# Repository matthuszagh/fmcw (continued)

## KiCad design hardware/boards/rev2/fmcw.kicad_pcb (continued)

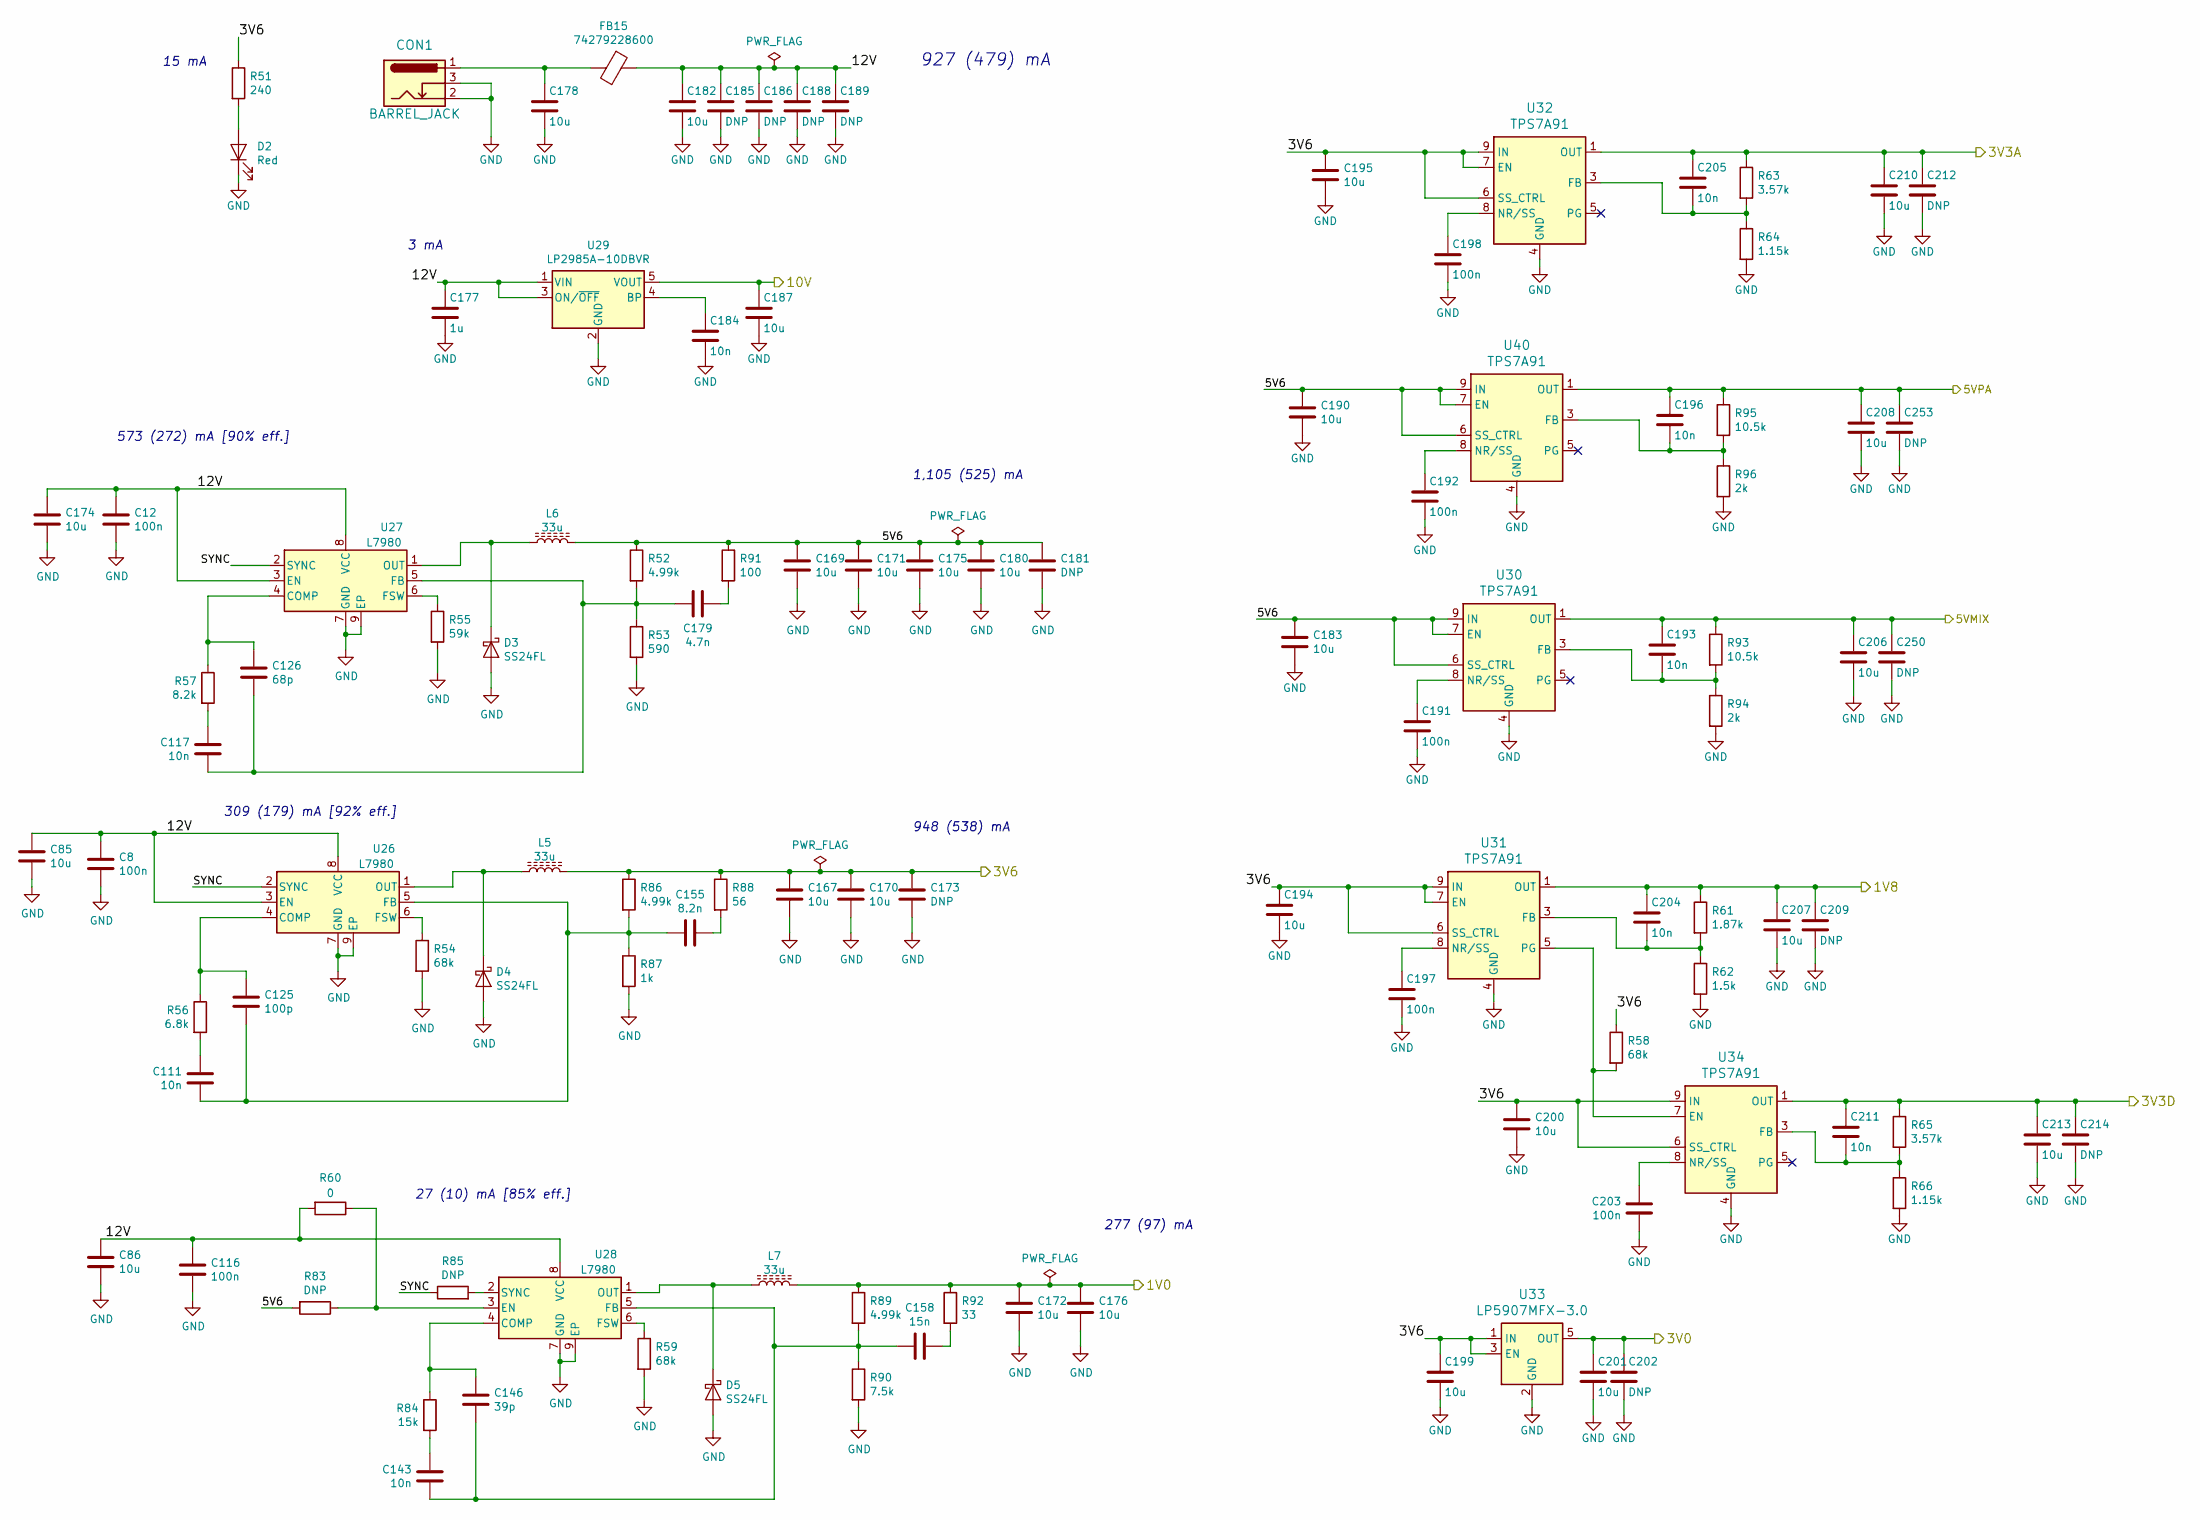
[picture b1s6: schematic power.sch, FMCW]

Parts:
C8, C12, C116, C191, C192, C197, C198, C203: 100n; C_0402_1005Metric
C85, C86, C167, C169, C170, C171, C172, C174, C175, C176, C178, C180, C182, C183, C187, C190, C194, C195, C199, C200, C201, C206, C207, C208, C210, C213: 10u; C_0805_2012Metric
C111, C117, C143, C184, C193, C196, C204, C205, C211: 10n; C_0402_1005Metric
C125: 100p; C_0402_1005Metric
C126: 68p; C_0402_1005Metric
C146: 39p; C_0402_1005Metric
C155: 8.2n; C_0402_1005Metric
C158: 15n; C_0402_1005Metric
C173, C181, C185, C186, C188, C189, C202, C209, C212, C214, C250, C253: DNP; C_0805_2012Metric
C177: 1u; C_0603_1608Metric
C179: 4.7n; C_0402_1005Metric
CON1: BARREL_JACK; BarrelJack_Wuerth_6941xx301002
D2: Red; LED_0603_1608Metric
D3, D4, D5: SS24FL; D_SOD-123F
FB15: 74279228600; L_0603_1608Metric
L5, L6: 33u; L_Wuerth_HCI-1365
L7: 33u; SRR6040A
R51: 240; R_0402_1005Metric
R52, R86, R89: 4.99k; R_0402_1005Metric
R53: 590; R_0402_1005Metric
R54, R58, R59: 68k; R_0402_1005Metric
R55: 59k; R_0402_1005Metric
R56: 6.8k; R_0402_1005Metric
R57: 8.2k; R_0402_1005Metric
R60: 0; R_0402_1005Metric
R61: 1.87k; R_0402_1005Metric
R62: 1.5k; R_0402_1005Metric
R63, R65: 3.57k; R_0402_1005Metric
R64, R66: 1.15k; R_0402_1005Metric
R83, R85: DNP; R_0402_1005Metric
R84: 15k; R_0402_1005Metric
R87: 1k; R_0402_1005Metric
R88: 56; R_0402_1005Metric
R90: 7.5k; R_0402_1005Metric
R91: 100; R_0402_1005Metric
R92: 33; R_0402_1005Metric
R93, R95: 10.5k; R_0402_1005Metric
R94, R96: 2k; R_0402_1005Metric
U26, U27, U28: L7980; HSOP-8-1EP_3.9x4.9mm_P1.27mm_EP2.3x2.3mm_ThermalVias
U29: LP2985A-10DBVR; SOT-23-5
U30, U31, U32, U34, U40: TPS7A91; Texas_S-PDSO-N10_EP1.2x2mm
U33: LP5907MFX-3.0; SOT-23-5

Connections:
/1V0: C172.1, C176.1, L7.2, R89.1, R92.1; also elsewhere on the board
/1V8: C204.1, C207.1, C209.1, R61.1, U31.1 (OUT), U31.2 (OUT); also elsewhere on the board
/3V0: C201.1, C202.1, U33.5 (OUT); also elsewhere on the board
/3V3A: C205.1, C210.1, C212.1, R63.1, U32.1 (OUT), U32.2 (OUT); also elsewhere on the board
/3V6: C167.1, C170.1, C173.1, C194.1, C195.1, C199.1, C200.1, L5.2, R51.1, R58.1, R86.1, R88.1, U31.6 (SS_CTRL), U31.7 (EN), U31.9 (IN), U31.10 (IN), U32.6 (SS_CTRL), U32.7 (EN), U32.9 (IN), U32.10 (IN), U33.1 (IN), U33.3 (EN), U34.6 (SS_CTRL), U34.9 (IN), U34.10 (IN); also elsewhere on the board
/5VMIX: C193.1, C206.1, C250.1, R93.1, U30.1 (OUT), U30.2 (OUT); also elsewhere on the board
/5VPA: C196.1, C208.1, C253.1, R95.1, U40.1 (OUT), U40.2 (OUT); also elsewhere on the board
/10V: C187.1, U29.5 (VOUT); also elsewhere on the board
/power/5V6: C169.1, C171.1, C175.1, C180.1, C181.1, C183.1, C190.1, L6.2, R52.1, R83.2, R91.1, U30.6 (SS_CTRL), U30.7 (EN), U30.9 (IN), U30.10 (IN), U40.6 (SS_CTRL), U40.7 (EN), U40.9 (IN), U40.10 (IN)
/power/12V: C8.1, C12.1, C85.1, C86.1, C116.1, C174.1, C177.1, C182.1, C185.1, C186.1, C188.1, C189.1, FB15.1, R60.2, U26.3 (EN), U26.8 (VCC), U27.3 (EN), U27.8 (VCC), U28.8 (VCC), U29.1 (VIN), U29.3 (ON/~OFF~)
/power/SYNC: R85.1, U26.2 (SYNC), U27.2 (SYNC)
GND: C8.2, C12.2, C85.2, C86.2, C116.2, C167.2, C169.2, C170.2, C171.2, C172.2, C173.2, C174.2, C175.2, C176.2, C177.2, C178.2, C180.2, C181.2, C182.2, C183.2, C184.2, C185.2, C186.2, C187.2, C188.2, C189.2, C190.2, C191.2, C192.2, C194.2, C195.2, C197.2, C198.2, C199.2, C200.2, C201.2, C202.2, C203.2, C206.2, C207.2, C208.2, C209.2, C210.2, C212.2, C213.2, C214.2, C250.2, C253.2, CON1.2, CON1.3, D2.1 (K), D3.2 (A), D4.2 (A), D5.2 (A), R53.2, R54.2, R55.2, R59.2, R62.2, R64.2, R66.2, R87.2, R90.2, R94.2, R96.2, U26.7 (GND), U26.9 (EP), U27.7 (GND), U27.9 (EP), U28.7 (GND), U28.9 (EP), U29.2 (GND), U30.4 (GND), U30.11 (GND), U31.4 (GND), U31.11 (GND), U32.4 (GND), U32.11 (GND), U33.2 (GND), U34.4 (GND), U34.11 (GND), U40.4 (GND), U40.11 (GND); also elsewhere on the board
unnamed: C111.1, R56.2
unnamed: C111.2, C125.2, C155.2, R86.2, R87.1, U26.5 (FB)
unnamed: C117.1, R57.2
unnamed: C117.2, C126.2, C179.2, R52.2, R53.1, U27.5 (FB)
unnamed: C125.1, R56.1, U26.4 (COMP)
unnamed: C126.1, R57.1, U27.4 (COMP)
unnamed: C143.1, R84.2
unnamed: C143.2, C146.2, C158.2, R89.2, R90.1, U28.5 (FB)
unnamed: C146.1, R84.1, U28.4 (COMP)
unnamed: C155.1, R88.2
unnamed: C158.1, R92.2
unnamed: C178.1, CON1.1, FB15.2
unnamed: C179.1, R91.2
unnamed: C184.1, U29.4 (BP)
unnamed: C191.1, U30.8 (NR/SS)
unnamed: C192.1, U40.8 (NR/SS)
unnamed: C193.2, R93.2, R94.1, U30.3 (FB)
unnamed: C196.2, R95.2, R96.1, U40.3 (FB)
unnamed: C197.1, U31.8 (NR/SS)
unnamed: C198.1, U32.8 (NR/SS)
unnamed: C203.1, U34.8 (NR/SS)
unnamed: C204.2, R61.2, R62.1, U31.3 (FB)
unnamed: C205.2, R63.2, R64.1, U32.3 (FB)
unnamed: C211.2, R65.2, R66.1, U34.3 (FB)
unnamed: D2.2 (A), R51.2
unnamed: D3.1 (K), L6.1, U27.1 (OUT)
unnamed: D4.1 (K), L5.1, U26.1 (OUT)
unnamed: D5.1 (K), L7.1, U28.1 (OUT)
unnamed: R54.1, U26.6 (FSW)
unnamed: R55.1, U27.6 (FSW)
unnamed: R58.2, U31.5 (PG), U34.7 (EN)
unnamed: R59.1, U28.6 (FSW)
unnamed: R60.1, R83.1, U28.3 (EN)
unnamed: R85.2, U28.2 (SYNC)

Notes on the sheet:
573 (272) mA [90% eff.]
15 mA
309 (179) mA [92% eff.]
3 mA
27 (10) mA [85% eff.]
1,105 (525) mA
948 (538) mA
927 (479) mA
277 (97) mA

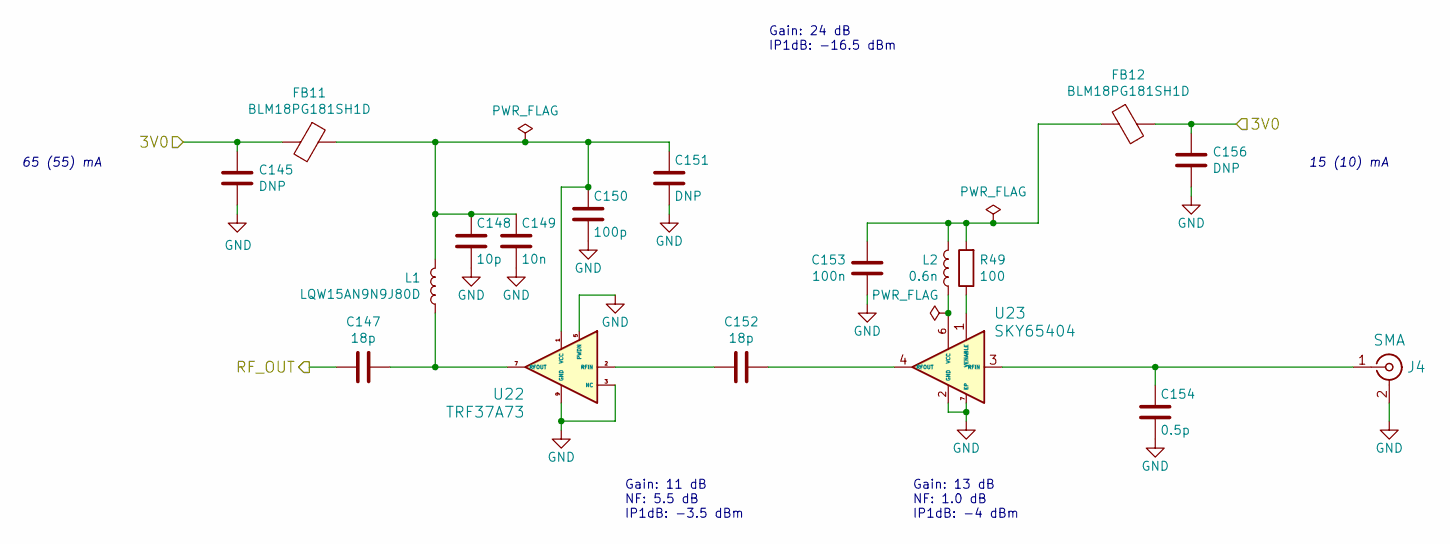
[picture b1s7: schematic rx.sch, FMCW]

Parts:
C145, C156: DNP; C_0805_2012Metric
C147, C152: 18p; RF_C_0201_0603Metric
C148: 10p; C_0402_1005Metric
C149: 10n; C_0402_1005Metric
C150: 100p; C_0402_1005Metric
C153: 100n; C_0402_1005Metric
C154: 0.5p; RF_C_0201_0603Metric
C163: DNP; C_0603_1608Metric
FB13, FB14: BLM18PG181SH1D; L_0603_1608Metric
J4: SMA; SMA_901-10512
L1: LQW15AN9N9J80D; RF_Bypass_C_0402_1005Metric
L2: 0.6n; L_0402_1005Metric
R49: 100; R_0402_1005Metric
U22: TRF37A73; WSON-8-1EP_2x2mm_P0.5mm_EP0.9x1.6mm_ThermalVias
U23: SKY65404; Skyworks_SKY65404-31

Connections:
/3V0: C145.1, C156.1, FB13.2, FB14.2; also elsewhere on the board
/RF1: C147.2; also elsewhere on the board
GND: C145.2, C148.2, C149.2, C150.2, C153.2, C154.2, C156.2, C163.2, J4.2 (Ext), U22.3 (NC), U22.4 (NC), U22.5 (PWDN), U22.6 (NC), U22.8 (NC), U22.9 (GND), U23.2 (GND), U23.5 (GND), U23.7 (EP); also elsewhere on the board
unnamed: C147.1, L1.1, U22.7 (RFOUT)
unnamed: C152.1, U23.4 (RFOUT)
unnamed: C152.2, U22.2 (RFIN)
unnamed: C154.1, J4.1 (In), U23.3 (RFIN)
unnamed: L2.1, U23.6 (VCC)
unnamed: R49.1, U23.1 (VENABLE)

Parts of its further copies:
C151: DNP; C_0603_1608Metric
C157, C168: DNP; C_0805_2012Metric
C159, C164: 18p; RF_C_0201_0603Metric
C160: 10p; C_0402_1005Metric
C161: 10n; C_0402_1005Metric
C162: 100p; C_0402_1005Metric
C165: 100n; C_0402_1005Metric
C166: 0.5p; RF_C_0201_0603Metric
FB11, FB12: BLM18PG181SH1D; L_0603_1608Metric
J5: SMA; SMA_901-10512
L3: LQW15AN9N9J80D; RF_Bypass_C_0402_1005Metric
L4: 0.6n; L_0402_1005Metric
R50: 100; R_0402_1005Metric
U24: TRF37A73; WSON-8-1EP_2x2mm_P0.5mm_EP0.9x1.6mm_ThermalVias
U25: SKY65404; Skyworks_SKY65404-31

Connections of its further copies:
/3V0: C157.1, C168.1, FB11.2, FB12.2; also elsewhere on the board
/RF2: C159.2; also elsewhere on the board
GND: C151.2, C157.2, C160.2, C161.2, C162.2, C165.2, C166.2, C168.2, J5.2 (Ext), U24.3 (NC), U24.4 (NC), U24.5 (PWDN), U24.6 (NC), U24.8 (NC), U24.9 (GND), U25.2 (GND), U25.5 (GND), U25.7 (EP); also elsewhere on the board
unnamed: C159.1, L3.1, U24.7 (RFOUT)
unnamed: C164.1, U25.4 (RFOUT)
unnamed: C164.2, U24.2 (RFIN)
unnamed: C166.1, J5.1 (In), U25.3 (RFIN)
unnamed: L4.1, U25.6 (VCC)
unnamed: R50.1, U25.1 (VENABLE)

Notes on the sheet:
65 (55) mA
Gain: 11 dB NF: 5.5 dB IP1dB: -3.5 dBm
Gain: 24 dB IP1dB: -16.5 dBm
Gain: 13 dB NF: 1.0 dB IP1dB: -4 dBm
15 (10) mA

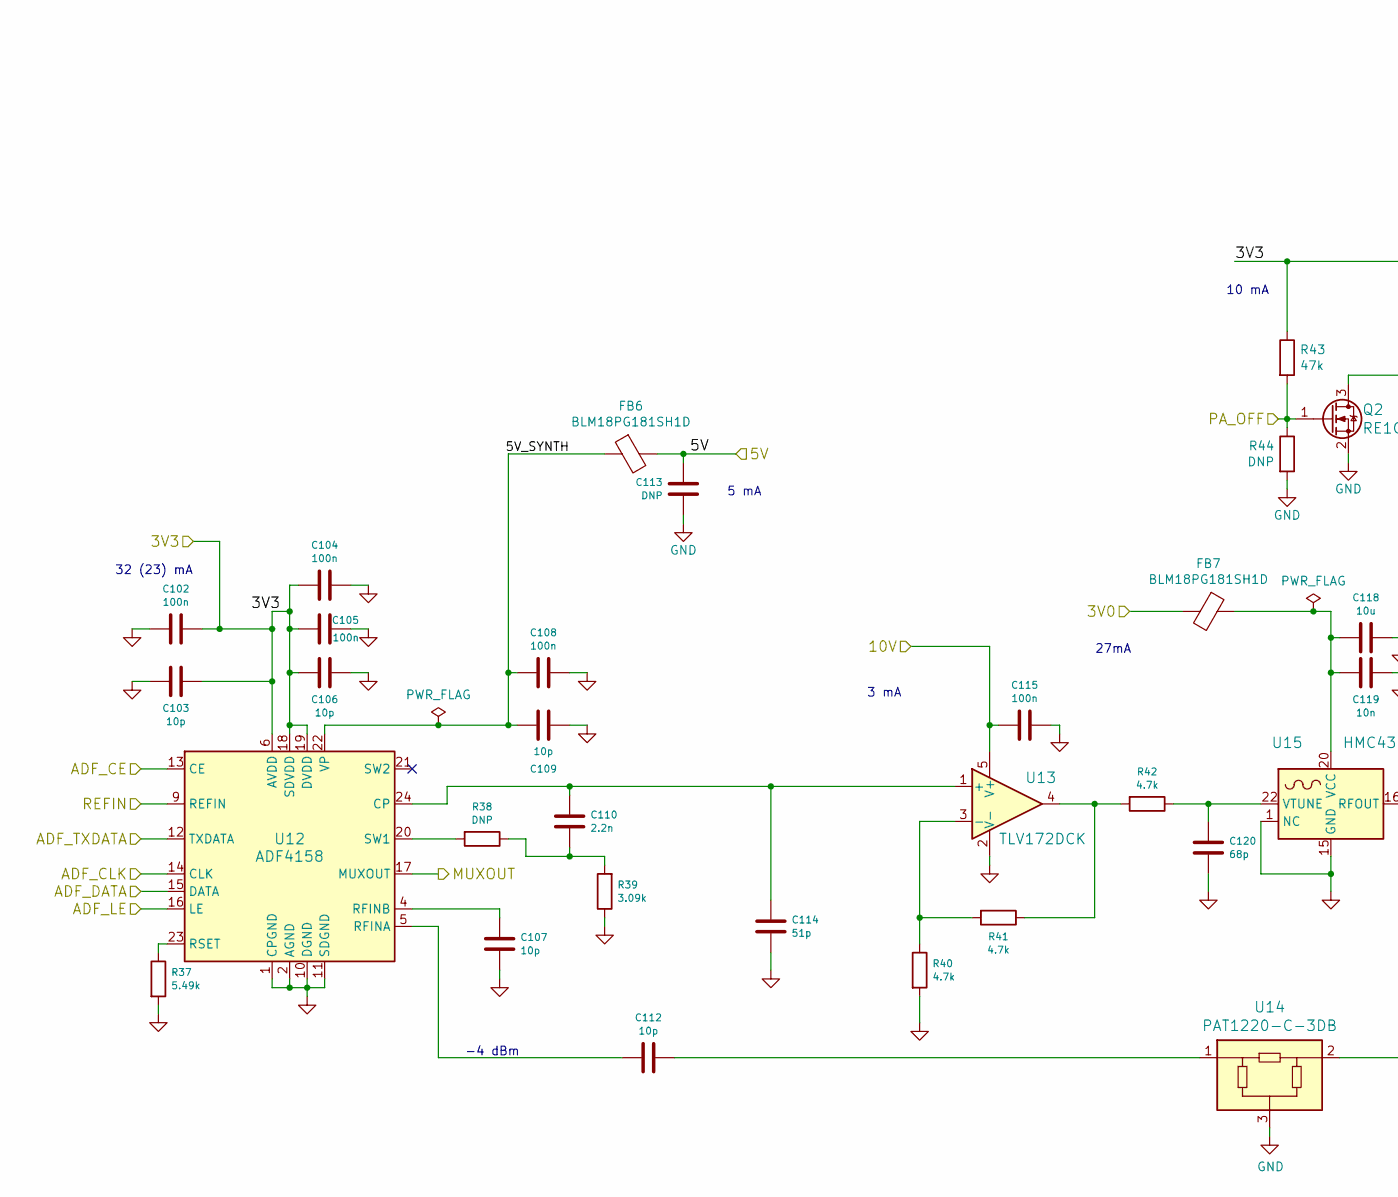
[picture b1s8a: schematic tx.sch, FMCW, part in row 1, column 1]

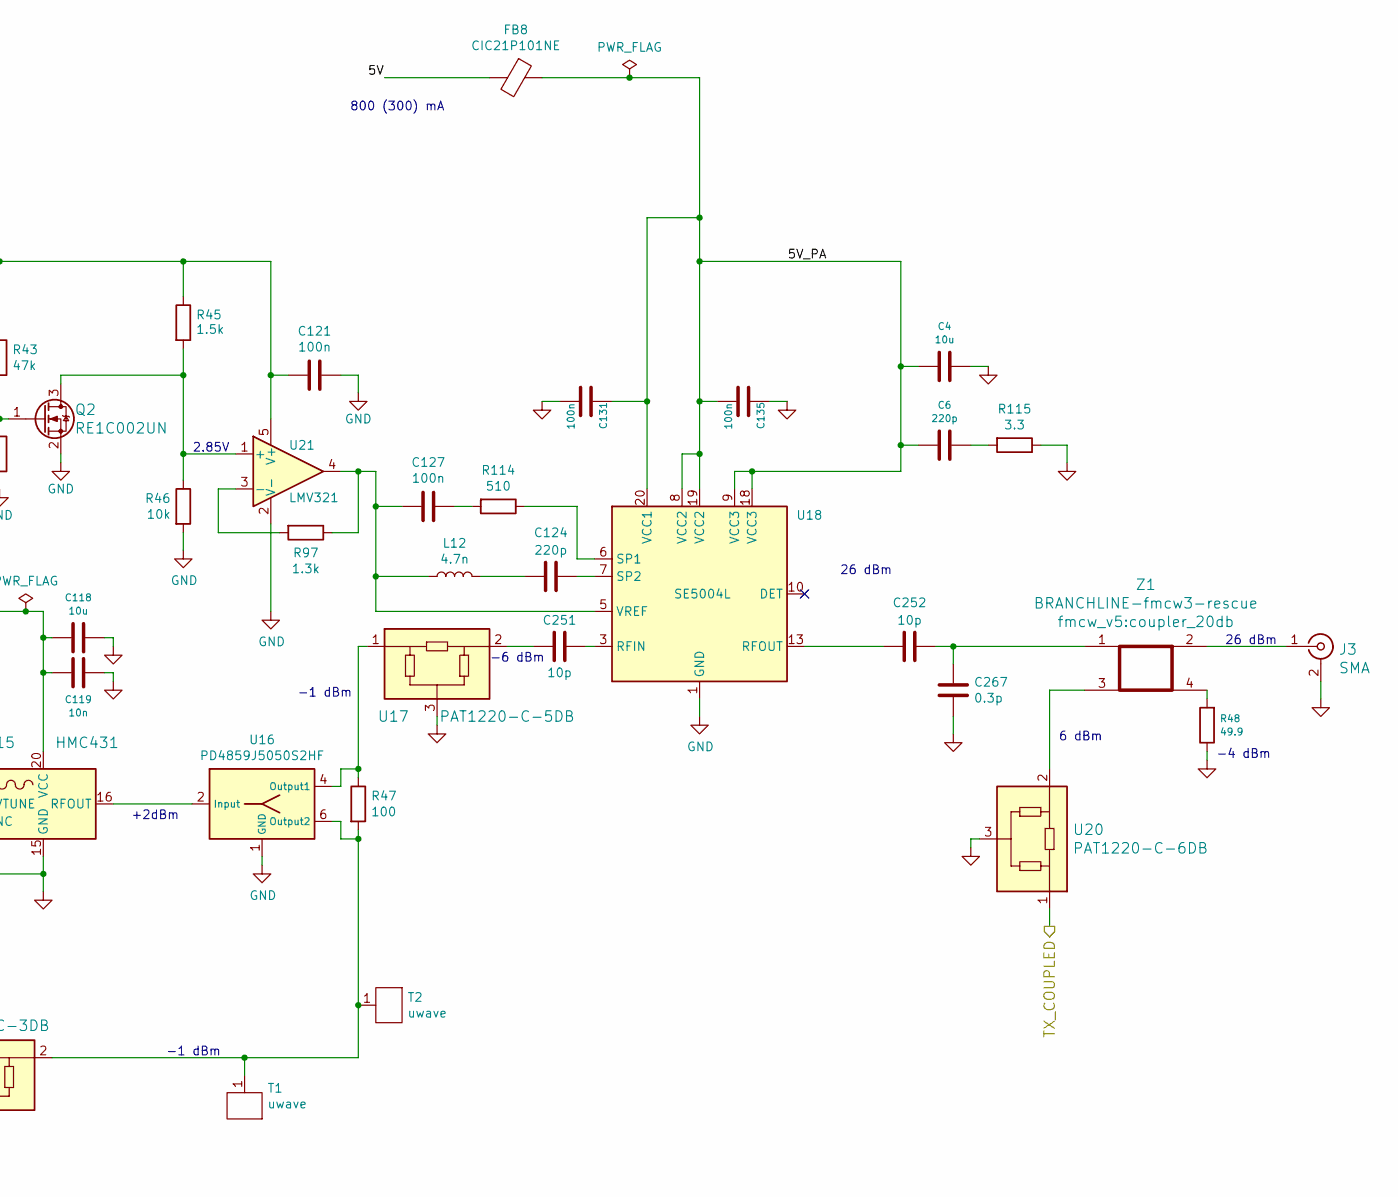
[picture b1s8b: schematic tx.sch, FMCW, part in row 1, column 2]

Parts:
C4, C118: 10u; C_0805_2012Metric
C6, C124: 220p; C_0402_1005Metric
C102, C104, C105, C108, C115, C121, C127, C131, C135: 100n; C_0402_1005Metric
C103, C106, C107, C109: 10p; C_0402_1005Metric
C110: 2.2n; C_0402_1005Metric
C112, C251, C252: 10p; RF_C_0201_0603Metric
C113: DNP; C_0805_2012Metric
C114: 51p; C_0402_1005Metric
C119: 10n; C_0402_1005Metric
C120: 68p; C_0402_1005Metric
C267: 0.3p; RF_C_0201_0603Metric
FB6, FB7: BLM18PG181SH1D; L_0603_1608Metric
FB8: CIC21P101NE; L_0805_2012Metric
J3: SMA; SMA_901-10512
L12: 4.7n; L_0402_1005Metric
Q2: RE1C002UN; SOT-416
R37: 5.49k; R_0402_1005Metric
R38, R44: DNP; R_0402_1005Metric
R39: 3.09k; R_0402_1005Metric
R40, R41, R42: 4.7k; R_0402_1005Metric
R43: 47k; R_0402_1005Metric
R45: 1.5k; R_0402_1005Metric
R46: 10k; R_0402_1005Metric
R47: 100; R_0603b
R48: 49.9; R_0402_1005Metric
R97: 1.3k; R_0402_1005Metric
R114: 510; R_0402_1005Metric
R115: 3.3; R_0402_1005Metric
T1, T2: uwave; uwm_0.38_0.17_90
U12: ADF4158; LFCSP-24-1EP_4x4mm_P0.5mm_EP2.5x2.5mm_ThermalVias
U13: TLV172DCK; SOT-353_SC-70-5
U14: PAT1220-C-3DB; RF_Attenuator_Susumu_PAT1220
U15: HMC431; QFN-24-1EP_4x4mm_P0.5mm_EP2.8x2.8mm_ThermalVias
U16: PD4859J5050S2HF; Anaren_0805_2012Metric-6
U17: PAT1220-C-5DB; RF_Attenuator_Susumu_PAT1220
U18: SE5004L; Skyworks_SE5004L
U20: PAT1220-C-6DB; RF_Attenuator_Susumu_PAT1220
U21: LMV321; SOT-23-5
Z1: BRANCHLINE-fmcw3-rescue; coupler_20db

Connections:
/3V0: FB7.2; also elsewhere on the board
/3V3A: C102.1, C103.1, C104.1, C105.1, C106.1, C121.2, R43.1, R45.1, U12.6 (AVDD), U12.7 (AVDD), U12.8 (AVDD), U12.18 (SDVDD), U12.19 (DVDD), U21.5 (V+); also elsewhere on the board
/5VPA: C113.1, FB6.2, FB8.2; also elsewhere on the board
/10V: C115.2, U13.5 (V+); also elsewhere on the board
/ADF_CE: U12.13 (CE); also elsewhere on the board
/ADF_CLK: U12.14 (CLK); also elsewhere on the board
/ADF_DATA: U12.15 (DATA); also elsewhere on the board
/ADF_LE: U12.16 (LE); also elsewhere on the board
/ADF_MUXOUT: U12.17 (MUXOUT); also elsewhere on the board
/ADF_REF: U12.9 (REFIN); also elsewhere on the board
/ADF_TXDATA: U12.12 (TXDATA); also elsewhere on the board
/LO: U20.1; also elsewhere on the board
/PA_OFF: Q2.1 (G), R43.2, R44.1; also elsewhere on the board
/tx/5V_PA: C4.2, C6.2, C131.1, C135.2, FB8.1, U18.8 (VCC2), U18.9 (VCC3), U18.18 (VCC3), U18.19 (VCC2), U18.20 (VCC1)
/tx/5V_SYNTH: C108.1, C109.1, FB6.1, U12.22 (VP)
GND: C4.1, C102.2, C103.2, C104.2, C105.2, C106.2, C107.1, C108.2, C109.2, C113.2, C114.2, C115.1, C118.1, C119.1, C120.2, C121.1, C131.2, C135.1, C267.1, J3.2 (Ext), Q2.2 (S), R37.2, R39.1, R40.2, R44.2, R46.2, R48.1, R115.1, U12.1 (CPGND), U12.2 (AGND), U12.3 (AGND), U12.10 (DGND), U12.11 (SDGND), U12.25 (AGND), U13.2 (V-), U14.3, U15.1 (NC), U15.2 (NC), U15.3 (NC), U15.4 (NC), U15.5 (NC), U15.6 (NC), U15.7 (NC), U15.8 (NC), U15.9 (NC), U15.10 (NC), U15.11 (NC), U15.12 (NC), U15.13 (NC), U15.14 (NC), U15.15 (GND), U15.17 (NC), U15.18 (NC), U15.19 (NC), U15.21 (NC), U15.23 (NC), U15.24 (NC), U15.25 (GND), U16.1 (GND), U16.3 (GND), U16.5 (GND), U17.3, U18.1 (GND), U20.3, U21.2 (V-); also elsewhere on the board
unnamed: C6.1, R115.2
unnamed: C107.2, U12.4 (RFINB)
unnamed: C110.1, C114.1, U12.24 (CP), U13.1 (+)
unnamed: C110.2, R38.1, R39.2
unnamed: C112.1, U14.1
unnamed: C112.2, U12.5 (RFINA)
unnamed: C118.2, C119.2, FB7.1, U15.20 (VCC)
unnamed: C120.1, R42.1, U15.22 (VTUNE)
unnamed: C124.1, U18.7 (SP2)
unnamed: C124.2, L12.2
unnamed: C127.1, R114.2
unnamed: C127.2, L12.1, R97.1, U18.5 (VREF), U21.4
unnamed: C251.1, U18.3 (RFIN)
unnamed: C251.2, U17.2
unnamed: C252.1, C267.2, Z1.1
unnamed: C252.2, U18.13 (RFOUT)
unnamed: J3.1 (In), Z1.2
unnamed: Q2.3 (D), R45.2, R46.1, U21.1 (+)
unnamed: R37.1, U12.23 (RSET)
unnamed: R38.2, U12.20 (SW1)
unnamed: R40.1, R41.2, U13.3 (-)
unnamed: R41.1, R42.2, U13.4
unnamed: R47.1, U16.4 (Output1), U17.1
unnamed: R47.2, T1.1, T2.1, U14.2, U16.6 (Output2)
unnamed: R48.2, Z1.4
unnamed: R97.2, U21.3 (-)
unnamed: R114.1, U18.6 (SP1)
unnamed: U15.16 (RFOUT), U16.2 (Input)
unnamed: U20.2, Z1.3

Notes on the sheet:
32 (23) mA
-4 dBm
5 mA
3 mA
27mA
10 mA
+2dBm
-1 dBm
2.85V
800 (300) mA
-6 dBm
26 dBm
6 dBm

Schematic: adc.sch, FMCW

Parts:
C75: 10u; C_0805_2012Metric
C76, C92, C93, C94: 2.2u; C_0603_1608Metric
C77, C84, C87, C88, C89, C90: 1u; C_0603_1608Metric
C78, C79, C80, C81, C82, C83: 100p; C_0402_1005Metric
C91, C95, C96, C97, C98, C99, C100, C101: 100n; C_0402_1005Metric
R28, R29, R30, R31: 49.9; R_0402_1005Metric
R32, R34, R35: 0; R_0402_1005Metric
R33: DNP; R_0402_1005Metric
R36: 22; R_0402_1005Metric
U10: LP5907MFX-3.0; SOT-23-5
U11: LTC2292; QFN-64-1EP_9x9mm_P0.5mm_EP7.15x7.15mm_ThermalVias

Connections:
/3V6: C75.1, U10.1 (IN), U10.3 (EN); also elsewhere on the board
/ADC1+: R31.2; also elsewhere on the board
/ADC1-: R29.2; also elsewhere on the board
/ADC2+: R30.2; also elsewhere on the board
/ADC2-: R28.2; also elsewhere on the board
/ADC_REF: R36.2, U11.8 (CLKA), U11.9 (CLKB); also elsewhere on the board
/ADC_VCM1: C92.2, U11.61 (VCMA); also elsewhere on the board
/ADC_VCM2: C76.1, U11.20 (VCMB); also elsewhere on the board
/fpga/ADC_OE1: U11.58 (~OEA); also elsewhere on the board
/fpga/ADC_OE2: U11.23 (~OEB); also elsewhere on the board
/fpga/ADC_SHDN1: U11.22 (SHDNB); also elsewhere on the board
/fpga/ADC_SHDN2: U11.59 (SHDNA); also elsewhere on the board
/fpga/D0: U11.43 (DA0); also elsewhere on the board
/fpga/D1: U11.44 (DA1); also elsewhere on the board
/fpga/D2: U11.45 (DA2); also elsewhere on the board
/fpga/D3: U11.46 (DA3); also elsewhere on the board
/fpga/D4: U11.47 (DA4); also elsewhere on the board
/fpga/D5: U11.48 (DA5); also elsewhere on the board
/fpga/D6: U11.51 (DA6); also elsewhere on the board
/fpga/D7: U11.52 (DA7); also elsewhere on the board
/fpga/D8: U11.53 (DA8); also elsewhere on the board
/fpga/D9: U11.54 (DA9); also elsewhere on the board
/fpga/D10: U11.55 (DA10); also elsewhere on the board
/fpga/D11: U11.56 (DA11); also elsewhere on the board
/fpga/OF1: U11.57 (OFA); also elsewhere on the board
/fpga/OF2: U11.40 (OFB); also elsewhere on the board
/fpga/adc/3V0: C77.1, C84.1, C91.1, C95.1, C98.1, C99.1, R32.1, R34.2, R35.2, U10.5 (OUT), U11.7 (VDD), U11.10 (VDD), U11.18 (VDD), U11.63 (VDD)
/fpga/adc/AINA+: C78.2, C79.1, R28.1, U11.1 (AINA+)
/fpga/adc/AINA-: C79.2, C80.1, R30.1, U11.2 (AINA-)
/fpga/adc/AINB+: C81.2, C82.1, R29.1, U11.16 (AINB+)
/fpga/adc/AINB-: C82.2, C83.1, R31.1, U11.15 (AINB-)
GND: C75.2, C76.2, C77.2, C78.1, C80.2, C81.1, C83.2, C84.2, C87.2, C88.2, C89.2, C90.2, C91.2, C92.1, C95.2, C98.2, C99.2, C100.2, C101.2, R33.2, U10.2 (GND), U11.17 (GND), U11.31 (OGND), U11.50 (OGND), U11.64 (GND), U11.65 (GND); also elsewhere on the board
unnamed: C87.1, C93.1, C96.1, U11.3 (REFHA), U11.4 (REFHA)
unnamed: C88.1, C93.2, C96.2, U11.5 (REFLA), U11.6 (REFLA)
unnamed: C89.1, C94.1, C97.1, U11.13 (REFHB), U11.14 (REFHB)
unnamed: C90.1, C94.2, C97.2, U11.11 (REFLB), U11.12 (REFLB)
unnamed: R32.2, R33.1, U11.60 (MODE)
unnamed: R34.1, U11.62 (SENSEA)
unnamed: R35.1, U11.19 (SENSEB)
unnamed: R36.1, U11.21 (MUX)

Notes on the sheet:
95 (78) mA
3 mA

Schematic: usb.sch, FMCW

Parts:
C59, C62, C63, C64, C65, C69, C70, C71, C72, C73, C74: 100n; C_0402_1005Metric
C60, C61: 15p; C_0402_1005Metric
C66, C67, C68: 4.7u; C_0603_1608Metric
FB3, FB4: BLM18PG181SH1D; L_0603_1608Metric
J2: USB_B_Micro; USB_Micro-B_Amphenol_10103594-0001LF_Horizontal
R3, R17, R27, R82: 10k; R_0402_1005Metric
R18: 2.2k; R_0402_1005Metric
R19: 12k; R_0402_1005Metric
R20, R21: 0; R_0402_1005Metric
R22: 1k; R_0402_1005Metric
R23, R24, R25: 33; R_0402_1005Metric
R26: 4.7k; R_0402_1005Metric
U8: 93LCxxBxxOT; SOT-23-6
U9: FT2232H; LQFP-64_10x10mm_P0.5mm
Y1: 12MHz; ABM10

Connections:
/fpga/CLKOUT: U9.32 (ACBUS5); also elsewhere on the board
/fpga/FT_D0: U9.16 (ADBUS0); also elsewhere on the board
/fpga/FT_D1: U9.17 (ADBUS1); also elsewhere on the board
/fpga/FT_D2: U9.18 (ADBUS2); also elsewhere on the board
/fpga/FT_D3: U9.19 (ADBUS3); also elsewhere on the board
/fpga/FT_D4: U9.21 (ADBUS4); also elsewhere on the board
/fpga/FT_D5: U9.22 (ADBUS5); also elsewhere on the board
/fpga/FT_D6: U9.23 (ADBUS6); also elsewhere on the board
/fpga/FT_D7: U9.24 (ADBUS7); also elsewhere on the board
/fpga/FT_SUSPEND: U9.36 (~SUSPEND); also elsewhere on the board
/fpga/OE#: U9.33 (ACBUS6); also elsewhere on the board
/fpga/RD#: U9.28 (ACBUS2); also elsewhere on the board
/fpga/RXF#: U9.26 (ACBUS0); also elsewhere on the board
/fpga/SIWUA: U9.30 (ACBUS4); also elsewhere on the board
/fpga/TCK: R23.1; also elsewhere on the board
/fpga/TDI: R25.1; also elsewhere on the board
/fpga/TDO: U9.40 (BDBUS2); also elsewhere on the board
/fpga/TMS: R24.1; also elsewhere on the board
/fpga/TXE#: U9.27 (ACBUS1); also elsewhere on the board
/fpga/WR: U9.29 (ACBUS3); also elsewhere on the board
/fpga/usb/1V8: C62.1, C63.1, C64.1, C67.1, U9.12 (VCORE), U9.37 (VCORE), U9.49 (VREGOUT), U9.64 (VCORE)
/fpga/usb/DO: R17.2, R18.1, U8.1 (DO)
/fpga/usb/EECLK: R3.2, U8.4 (CLK), U9.62 (EECLK)
/fpga/usb/EECS: R82.2, U8.5 (CS), U9.63 (EECS)
/fpga/usb/EEDATA: R18.2, U8.3 (DI), U9.61 (EEDATA)
/fpga/usb/USBD_N: R20.1, U9.7 (DM)
/fpga/usb/USBD_P: R21.1, U9.8 (DP)
/fpga/usb/USBDa_N: J2.2 (D-), R20.2
/fpga/usb/USBDa_P: J2.3 (D+), R21.2
/fpga/usb/USB_5V: J2.1 (VBUS), R26.1
GND: C59.2, C60.2, C61.2, C62.2, C63.2, C64.2, C65.1, C66.2, C67.2, C68.2, C69.2, C70.2, C71.2, C72.2, C73.2, C74.2, J2.5 (GND), J2.6 (Shield), R19.2, R27.2, U8.2 (GND), U9.1 (GND), U9.5 (GND), U9.10 (AGND), U9.11 (GND), U9.13 (TEST), U9.15 (GND), U9.25 (GND), U9.35 (GND), U9.47 (GND), U9.51 (GND); also elsewhere on the board
unnamed: C60.1, U9.2 (OSCI), Y1.1
unnamed: C61.1, U9.3 (OSCO), Y1.3
unnamed: C66.1, C69.1, FB4.2, U9.4 (VPHY)
unnamed: C68.1, C70.1, FB3.1, U9.9 (VPLL)
unnamed: R19.1, U9.6 (REF)
unnamed: R22.1, U9.14 (~RESET)
unnamed: R23.2, U9.38 (BDBUS0)
unnamed: R24.2, U9.41 (BDBUS3)
unnamed: R25.2, U9.39 (BDBUS1)
unnamed: R26.2, R27.1, U9.59 (BCBUS7)

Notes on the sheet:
70 mA
150 mA

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
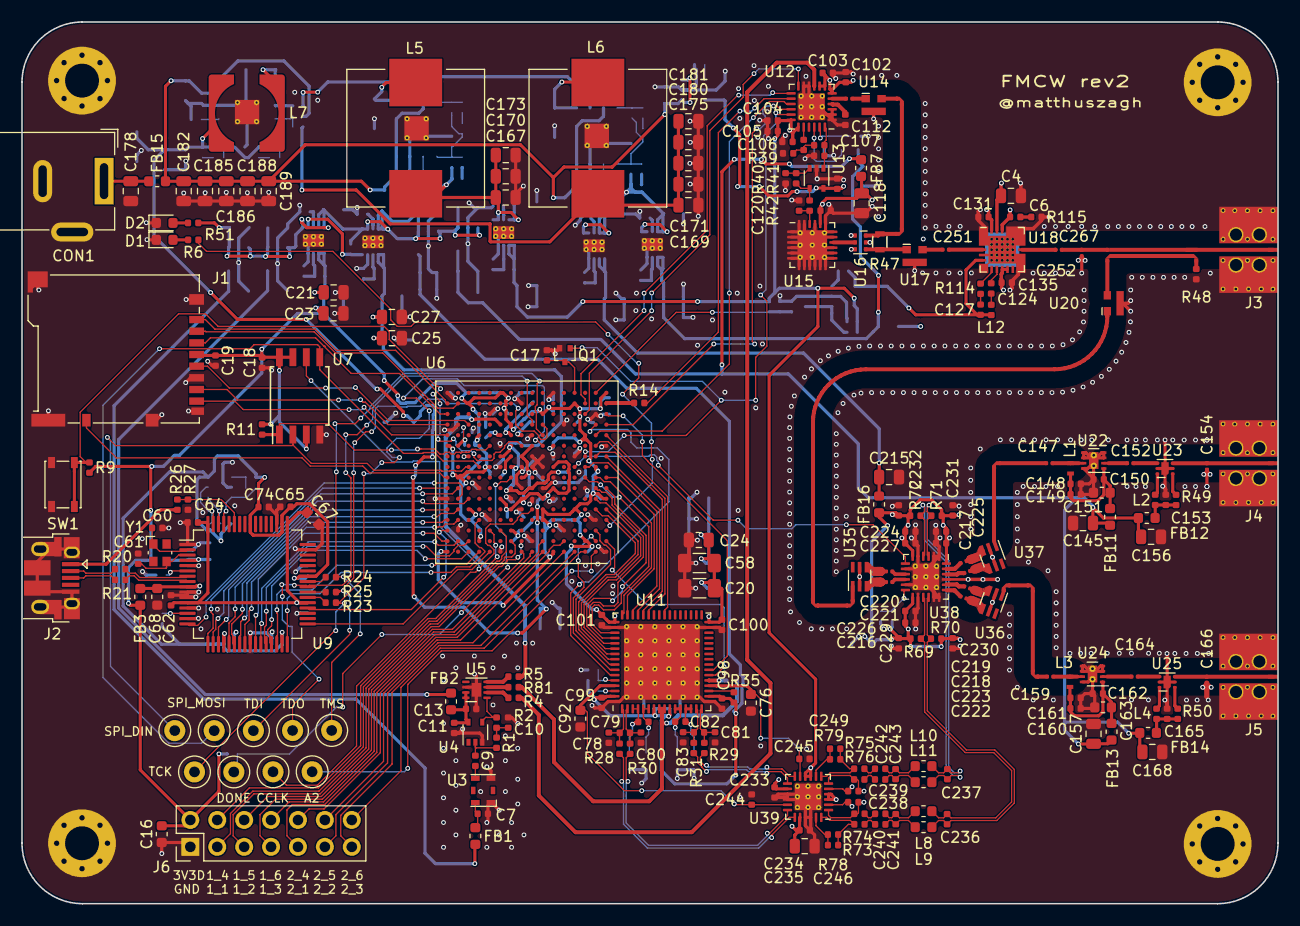
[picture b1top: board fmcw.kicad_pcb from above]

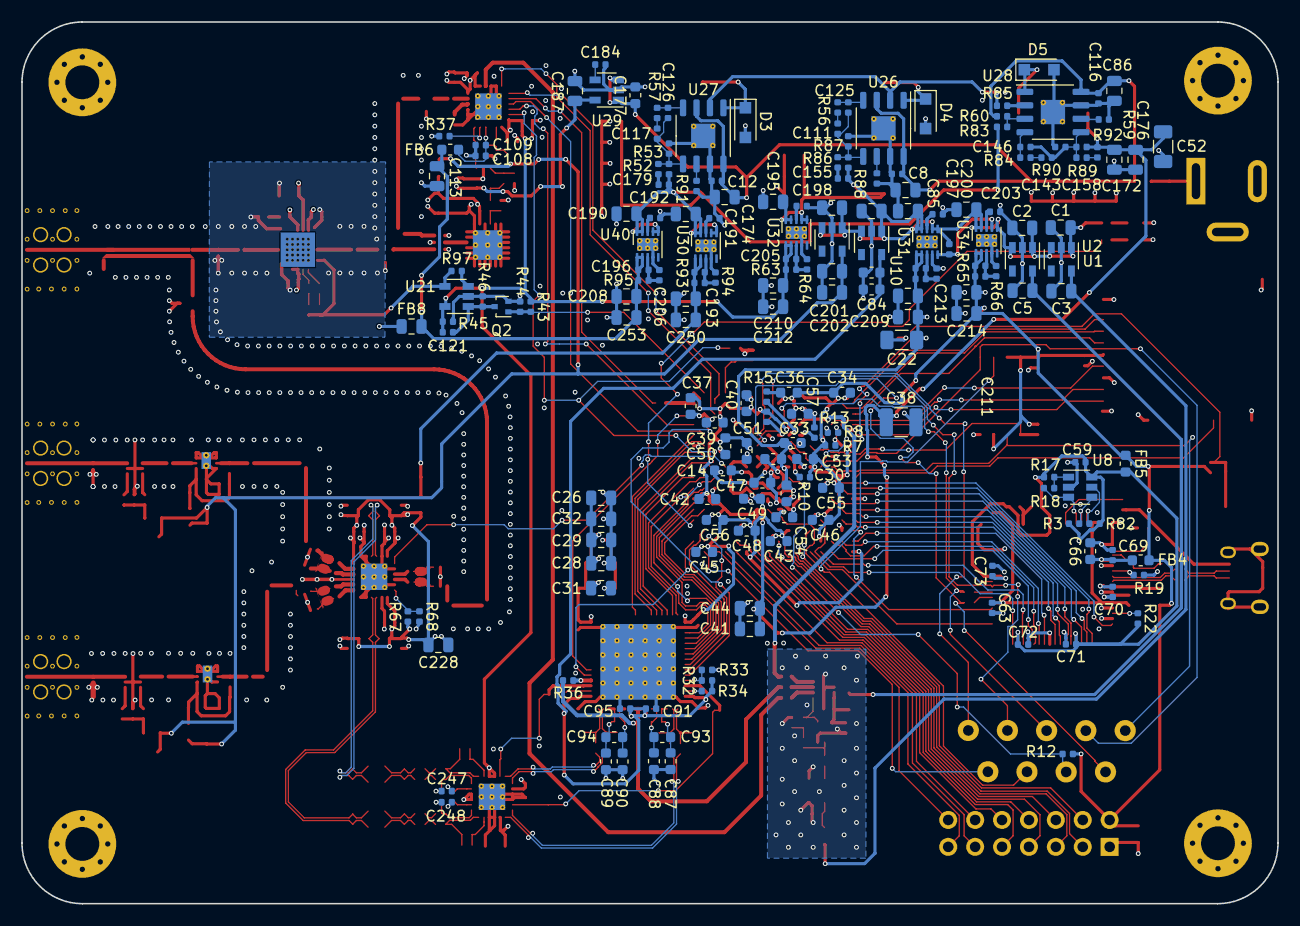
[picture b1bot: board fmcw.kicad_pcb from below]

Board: 4 copper layers, 118.6 x 83.2 mm, 445 parts (188 on the bottom side), 266 nets.

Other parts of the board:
FB5: BLM18PG181SH1D; L_0603_1608Metric
T9, T13, T14: uwave; balun_exit
T10, T11, T12: uwave; balun_exit_inv

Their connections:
/mixer/LOIa+: T9.1; also elsewhere on the board
/mixer/LOIa-: T10.1; also elsewhere on the board
/mixer/RF1a+: T11.1; also elsewhere on the board
/mixer/RF1a-: T13.1; also elsewhere on the board
/mixer/RF2a+: T12.1; also elsewhere on the board
/mixer/RF2a-: T14.1; also elsewhere on the board

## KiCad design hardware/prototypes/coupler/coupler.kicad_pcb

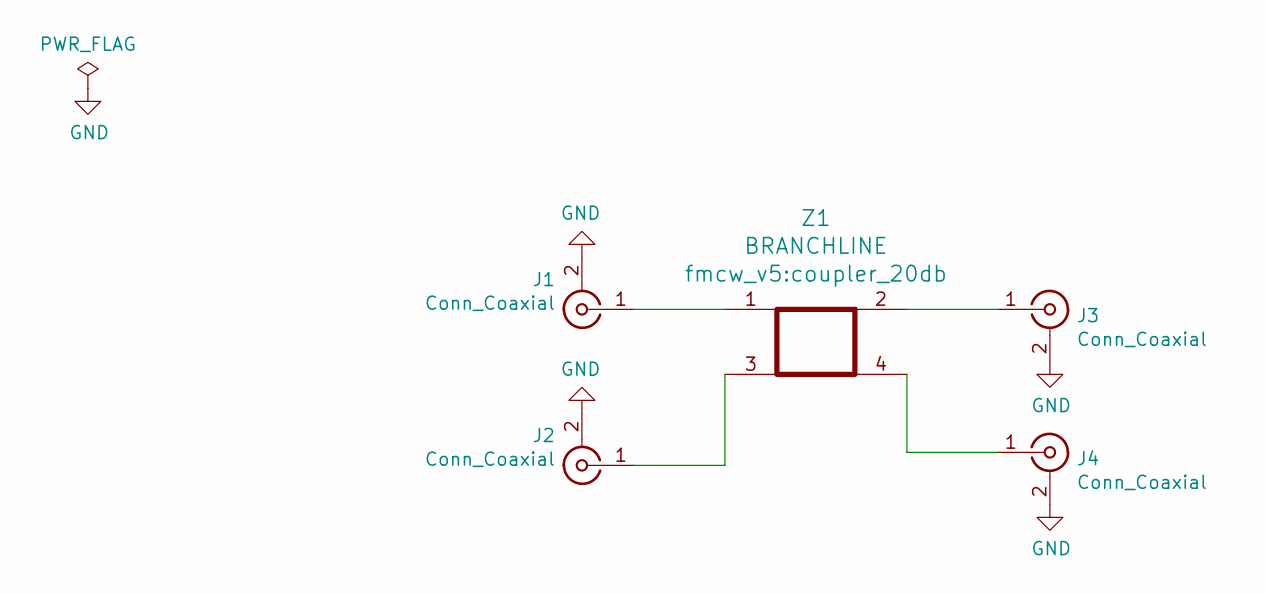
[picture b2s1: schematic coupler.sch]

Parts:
J1, J2, J3, J4: Conn_Coaxial; BU-1420701851_SMA
Z1: BRANCHLINE; coupler_20db

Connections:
GND: J1.2 (Ext), J2.2 (Ext), J3.2 (Ext), J4.2 (Ext)
unnamed: J1.1 (In), Z1.1
unnamed: J2.1 (In), Z1.3
unnamed: J3.1 (In), Z1.2
unnamed: J4.1 (In), Z1.4

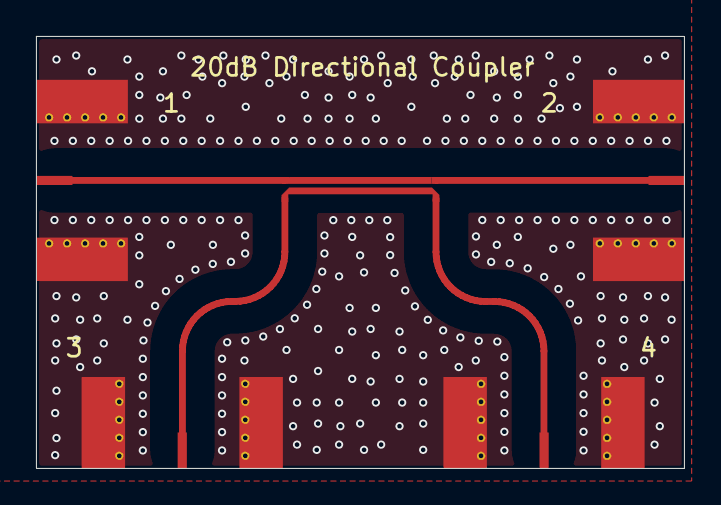
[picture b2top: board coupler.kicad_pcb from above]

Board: 4 copper layers, 36.0 x 24.0 mm, 5 parts (0 on the bottom side), 5 nets.
